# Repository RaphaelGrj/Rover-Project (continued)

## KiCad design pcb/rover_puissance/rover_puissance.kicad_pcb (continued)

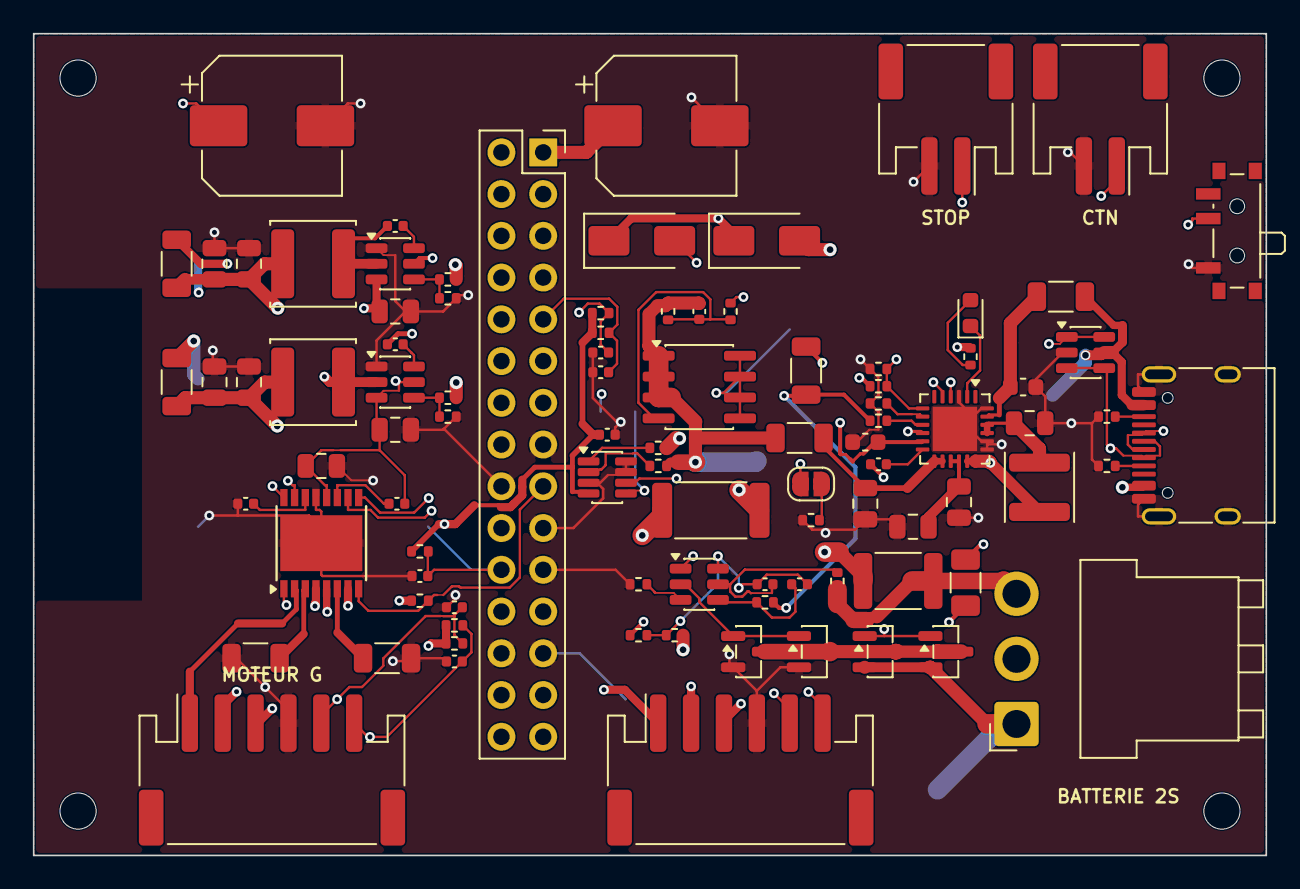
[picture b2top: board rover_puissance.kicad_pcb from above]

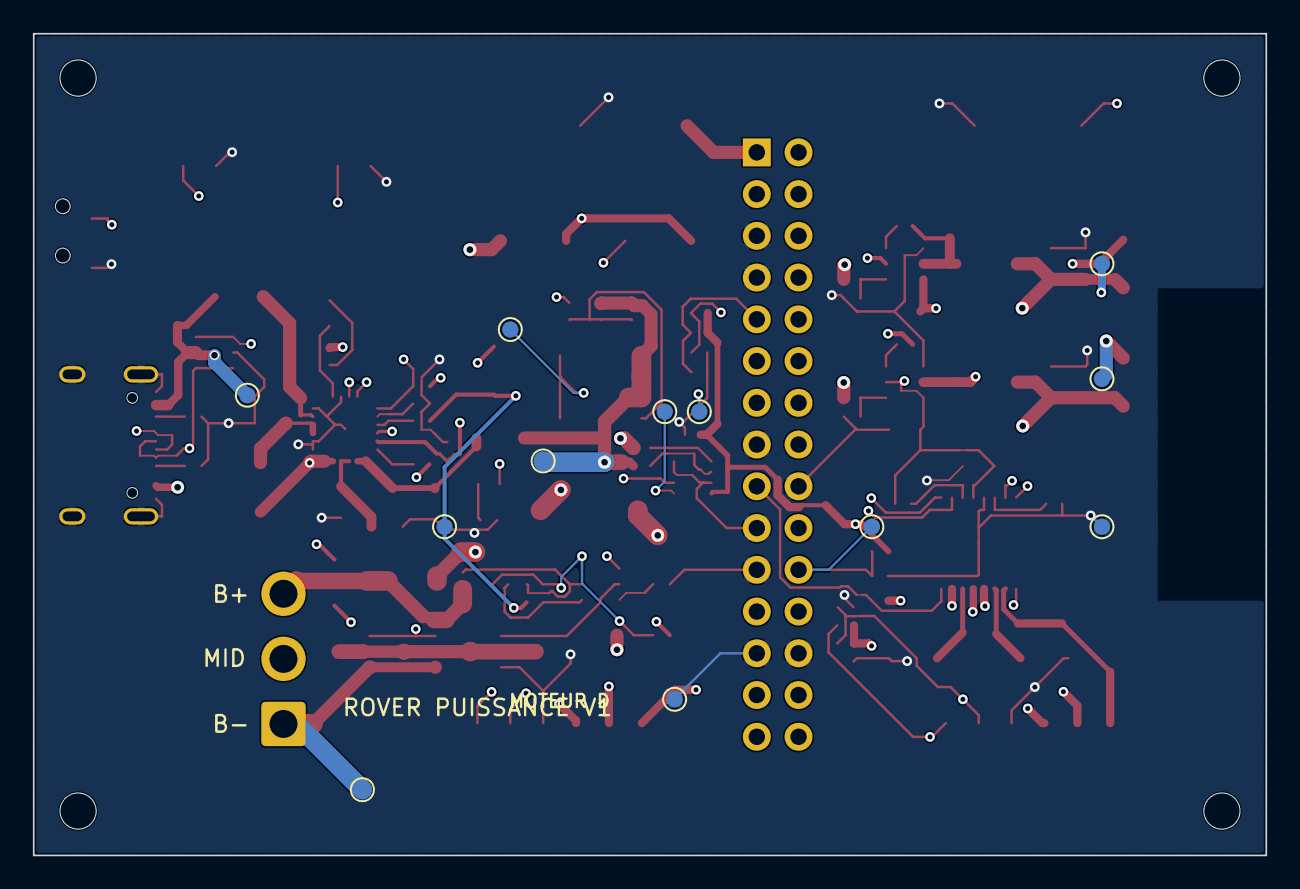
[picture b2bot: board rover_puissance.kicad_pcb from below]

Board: 4 copper layers, 75.0 x 50.0 mm, 109 parts (12 on the bottom side), 69 nets.

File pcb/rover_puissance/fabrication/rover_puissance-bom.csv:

Comment,Designator,Footprint,LCSC Part #
4.7uF,C10,C_0603_1608Metric,
47nF,C11,C_0402_1005Metric,
22uF 10V,"C162,C163,C152,C153",C_0805_2012Metric,
1uF 25V,C4,C_0603_1608Metric,
100nF,"C40,C12,C13,C14,C160,C150,C49",C_0402_1005Metric,
2.2uF 6.3V,C47,C_0402_1005Metric,
10nF 25V,C48,C_0402_1005Metric,
22uF 25V,"C5,C7,C8",C_0805_2012Metric,
470uF 16V,"C70,C45",CP_Elec_8x10,
10uF 25V,"C9,C161,C151,C46",C_0805_2012Metric,
LED orange (charge),D2,LED_0603_1608Metric,
SS34,"D4,D5",D_SMA,C717457
PTC 4A 16V (1812),F1,Fuse_1812_4532Metric,
PTC 0.75A (1206),F2,Fuse_1206_3216Metric,
USB-C TYPE-C-31-M-12,J1,USB_C_Receptacle_HRO_TYPE-C-31-M-12,C165948
Arret d'urgence (1:ESTOP_N 2:GND),J11,JST_PH_S2B-PH-SM4-TB_1x02-1MP_P2.00mm_Horizontal,C295747
CTN 10k cellules,J13,JST_PH_S2B-PH-SM4-TB_1x02-1MP_P2.00mm_Horizontal,C295747
Batterie 2S JST-VH coude (1:B- 2:MID 3:B+),J2,JST_VH_B3PS-VH_1x03_P3.96mm_Horizontal,C131336
Vers carte logique (embase 2x15),J20,PinSocket_2x15_P2.54mm_Vertical,
Moteur gauche (1:M1 2:M2 3:3V3 4:GND 5:A 6:B),J3,JST_PH_S6B-PH-SM4-TB_1x06-1MP_P2.00mm_Horizontal,C265405
Moteur droit (1:M1 2:M2 3:3V3 4:GND 5:A 6:B),J4,JST_PH_S6B-PH-SM4-TB_1x06-1MP_P2.00mm_Horizontal,C265405
1uH 4A (FNR4030S1R0),L1,L_Changjiang_FNR4030S,
3.3uH 3A (FNR5040S3R3),L15,L_Changjiang_FNR5040S,
2.2uH 3A (FNR5040S2R2),L16,L_Changjiang_FNR5040S,
AO3400A,"Q1,Q4,Q2,Q5",SOT-23,C20917
AO4407A,Q3,SOIC-8_3.9x4.9mm_P1.27mm,C16072
5.23k,R10,R_0402_1005Metric,
30.1k,R11,R_0402_1005Metric,
10k,"R12,R18,R161,R151,R25,R26,R30,R31,R32,R33",R_0402_1005Metric,
2.2k,R13,R_0402_1005Metric,
470,"R14,R15",R_0402_1005Metric,
54.9k,R150,R_0402_1005Metric,
2k,R16,R_0402_1005Metric,
33.2k,R160,R_0402_1005Metric,
0 (pont),"R162,R152",R_1206_3216Metric,
100k,R17,R_0402_1005Metric,
1M,R19,R_0402_1005Metric,
0.2 (limite 1A),"R23,R24",R_1206_3216Metric,
5.1k,"R5,R6",R_0402_1005Metric,
0 (pont batterie),R60,R_1206_3216Metric,
0 (pont VBUS),R61,R_1206_3216Metric,
10,"R62,R63",R_0402_1005Metric,
0 (pont mesure),R64,R_0402_1005Metric,
620,R7,R_0402_1005Metric,
330,R8,R_0402_1005Metric,
100,R9,R_1206_3216Metric,
0.05 1W (shunt),RS1,R_2512_6332Metric,
Marche/Arret,SW1,SW_SPDT_PCM12,
INA219AIDCNR,U16,SOT-23-8,C87469
USBLC6-2SC6,U2,SOT-23-6,C7519
BQ25887RGER,U3,Texas_RGE0024H_VQFN-24-1EP_4x4mm_P0.5mm_EP2.7x2.7mm,C2761614
S-8252AAC-M6T1U,U4,SOT-23-6,C468219
TPS563201DDCR,"U6,U5",SOT-23-6,C116592
DRV8833PWPR,U7,HTSSOP-16-1EP_4.4x5mm_P0.65mm_EP3.4x5mm,C50506

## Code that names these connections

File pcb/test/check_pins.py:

# -*- coding: utf-8 -*-
"""
Contrôle de cohérence carte <-> firmware, sans matériel.

Compare les GPIO câblés sur les deux cartes (pcb/gen/design_logique.py et
design_puissance.py) à ceux que le firmware
utilise pour cette carte (esp32/include/board_pins_pcb_v1.h). Une seule broche
différente et la fonction correspondante ne marcherait pas sur la carte réelle,
sans aucune erreur de compilation : c'est exactement ce que ce test attrape.

Usage (n'importe quel Python 3) :
    python pcb/test/check_pins.py
Code de retour 0 si tout concorde, 1 sinon.
"""
import os
import re
import sys

HERE = os.path.dirname(os.path.abspath(__file__))
sys.path.insert(0, os.path.join(HERE, "..", "gen"))
import design_logique as LOG      # noqa: E402
import design_puissance as PUI    # noqa: E402
import parts                      # noqa: E402

ALL_PARTS = {"logique": LOG.PARTS, "puissance": PUI.PARTS}

HEADER = os.path.join(HERE, "..", "..", "esp32", "include", "board_pins_pcb_v1.h")

# Constante du firmware -> nom du net sur la carte.
GPIO_NETS = {
    "ROVER_PIN_MOTOR_L_IN1": "ML_IN1", "ROVER_PIN_MOTOR_L_IN2": "ML_IN2",
    "ROVER_PIN_MOTOR_R_IN1": "MR_IN1", "ROVER_PIN_MOTOR_R_IN2": "MR_IN2",
    "ROVER_PIN_ENCODER_L_A": "ENC_L_A", "ROVER_PIN_ENCODER_L_B": "ENC_L_B",
    "ROVER_PIN_ENCODER_R_A": "ENC_R_A", "ROVER_PIN_ENCODER_R_B": "ENC_R_B",
    "ROVER_PIN_I2C_SDA": "SDA", "ROVER_PIN_I2C_SCL": "SCL", "ROVER_PIN_ESTOP": "ESTOP_N",
    "ROVER_PIN_SERVO_PITCH": "SERVO",
    "ROVER_PIN_DISPLAY_SCLK": "SCR_SCK", "ROVER_PIN_DISPLAY_MOSI": "SCR_MOSI", "ROVER_PIN_DISPLAY_DC": "SCR_DC",
    "ROVER_PIN_I2S_BCLK": "I2S_BCLK", "ROVER_PIN_I2S_LRC": "I2S_LRCLK", "ROVER_PIN_I2S_DIN": "I2S_DOUT",
    "ROVER_PIN_I2S_MIC_SD": "MIC_SD",
    "ROVER_PIN_CAM_XCLK": "CAM_XCLK", "ROVER_PIN_CAM_SIOD": "CAM_SIOD", "ROVER_PIN_CAM_SIOC": "CAM_SIOC",
    "ROVER_PIN_CAM_Y9": "CAM_Y9", "ROVER_PIN_CAM_Y8": "CAM_Y8", "ROVER_PIN_CAM_Y7": "CAM_Y7",
    "ROVER_PIN_CAM_Y6": "CAM_Y6", "ROVER_PIN_CAM_Y5": "CAM_Y5", "ROVER_PIN_CAM_Y4": "CAM_Y4",
    "ROVER_PIN_CAM_Y3": "CAM_Y3", "ROVER_PIN_CAM_Y2": "CAM_Y2", "ROVER_PIN_CAM_VSYNC": "CAM_VSYNC",
    "ROVER_PIN_CAM_HREF": "CAM_HREF", "ROVER_PIN_CAM_PCLK": "CAM_PCLK",
}
# Ligne de l'expandeur TCA9554 -> nom du net sur la carte.
EXP_NETS = {
    "ROVER_EXP_TOF_RIGHT_XSHUT": "XSHUT_R", "ROVER_EXP_AMP_ENABLE": "AMP_EN", "ROVER_EXP_CAM_PWDN": "CAM_PWDN",
    "ROVER_EXP_DISPLAY_RST": "SCR_RST", "ROVER_EXP_DISPLAY_BLK": "SCR_BLK", "ROVER_EXP_DRV_FAULT": "DRV_FAULT",
    "ROVER_EXP_STATUS_LED": "LED_ST", "ROVER_EXP_SPARE": "EXP_P7",
}
# Câblages fixes du cahier des charges (puce, nom de broche) -> net.
FIXED = [
    ("puissance", "U7", "AIN1", "ML_IN1"), ("puissance", "U7", "AIN2", "ML_IN2"),
    ("puissance", "U7", "BIN1", "MR_IN1"), ("puissance", "U7", "BIN2", "MR_IN2"),
    ("puissance", "U7", "nSLEEP", "ESTOP_N"), ("puissance", "U7", "nFAULT", "DRV_FAULT"),
    ("puissance", "U7", "VM", "VBAT_SYS"),
    ("logique", "U1", "IO19", "USB_DM"), ("logique", "U1", "IO20", "USB_DP"), ("logique", "U1", "IO0", "IO0"),
    ("logique", "U11", "SA0", "+3V3"),      # IMU en 0x6B (0x6A est pris par le chargeur)
    ("logique", "U12", "SDO", "GND"),       # BME688 en 0x76
    ("logique", "U13", "A0", "GND"), ("logique", "U13", "A1", "GND"), ("logique", "U13", "A2", "GND"),  # 0x20
    ("puissance", "U16", "A0", "GND"), ("puissance", "U16", "A1", "GND"),                               # 0x40
    ("logique", "J10", "7", "GND"),         # CS de l'écran à la masse (ROVER_PIN_DISPLAY_CS = -1)
]
# Signaux qui doivent traverser le connecteur inter-cartes (présents des deux côtés).
CROSSING = ["ML_IN1", "ML_IN2", "MR_IN1", "MR_IN2", "ENC_L_A", "ENC_L_B", "ENC_R_A", "ENC_R_B",
            "SDA", "SCL", "ESTOP_N", "DRV_FAULT", "USB_DP", "USB_DM", "+3V3", "+5V", "GND"]


def pins_by_name(board, ref):
    """{nom de broche: net} pour un composant d'une des deux cartes."""
    part = [p for p in ALL_PARTS[board] if p["ref"] == ref][0]
    names = parts.PIN_NAMES.get(part["kind"], {})
    out = {}
    for pad, net in part["pins"].items():
        key = int(pad) if pad.isdigit() else pad
        out[str(names.get(key, pad))] = net
    return out


def main():
    text = open(HEADER, encoding="utf8").read()
    consts = {m.group(1): int(m.group(2)) for m in
              re.finditer(r"constexpr\s+\w+\s+(ROVER_\w+)\s*=\s*(-?\d+)\s*;", text)}
    esp, exp = pins_by_name("logique", "U1"), pins_by_name("logique", "U13")
    errors, checked = [], 0
    for const, net in GPIO_NETS.items():
        gpio = consts.get(const)
        got = esp.get("IO%d" % gpio) if gpio is not None else None
        checked += 1
        if got != net:
            errors.append("%s = GPIO%s : la carte y relie '%s', attendu '%s'" % (const, gpio, got, net))
    for const, net in EXP_NETS.items():
        bit = consts.get(const)
        got = exp.get("P%d" % bit) if bit is not None else None
        checked += 1
        if got != net:
            errors.append("%s = P%s : la carte y relie '%s', attendu '%s'" % (const, bit, got, net))
    for board, ref, pin, net in FIXED:
        got = pins_by_name(board, ref).get(pin)
        checked += 1
        if got != net:
            errors.append("%s %s.%s : relie a '%s', attendu '%s'" % (board, ref, pin, got, net))
    # Connecteur inter-cartes : même net de part et d'autre de chaque rangée, et tous les
    # signaux partagés présents sur les deux cartes.
    sock, hdr = parts.conn_pins_socket(), parts.conn_pins_header()
    for row in range(15):
        left_s, right_s = sock[2 * row + 2], sock[2 * row + 1]
        left_h, right_h = hdr[2 * (14 - row) + 1], hdr[2 * (14 - row) + 2]
        checked += 1
        if (left_s, right_s) != (left_h, right_h):
            errors.append("connecteur rangee %d : puissance %s/%s, logique %s/%s" % (row, left_s, right_s, left_h, right_h))
    for net in CROSSING:
        for board, mod in (("puissance", PUI), ("logique", LOG)):
            checked += 1
            if len(mod.nets().get(net, [])) < 2:
                errors.append("%s : le signal %s n'arrive nulle part sur la carte" % (board, net))
    # Constantes de broches du firmware que ce test ne connait pas : a ajouter ci-dessus.
    unknown = [c for c in consts if (c.startswith("ROVER_PIN_") or c.startswith("ROVER_EXP_"))
               and c not in GPIO_NETS and c not in EXP_NETS and consts[c] >= 0
               and not c.endswith("_MASK") and not c.endswith("_OUTPUTS")]
    for c in unknown:
        errors.append("constante firmware non couverte par ce test : %s = %d" % (c, consts[c]))
    print("%d verifications, %d ecart(s)" % (checked, len(errors)))
    for e in errors:
        print("  ECART :", e)
    return 1 if errors else 0


if __name__ == "__main__":
    sys.exit(main())
